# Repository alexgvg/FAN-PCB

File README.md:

# FAN-PCB
Leiterkarte für FAN Stromverteilung

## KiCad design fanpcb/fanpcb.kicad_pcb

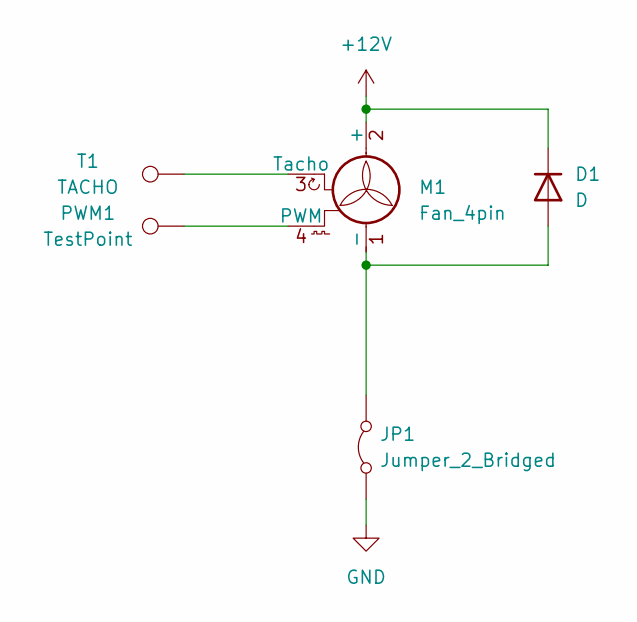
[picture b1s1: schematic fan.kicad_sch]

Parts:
D1: D; D_0603_1608Metric_Pad1.05x0.95mm_HandSolder
JP1: Jumper_2_Bridged; PinHeader_1x02_P2.54mm_Vertical
M1: Fan_4pin; FanPinHeader_1x04_P2.54mm_Vertical
PWM1: TestPoint; TestPoint_Pad_D2.5mm
T1: TACHO; TestPoint_Pad_D2.5mm

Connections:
+12V: D1.1 (K), M1.2 (+); also elsewhere on the board
GND: JP1.1 (A); also elsewhere on the board
unnamed: D1.2 (A), JP1.2 (B), M1.1 (-)
unnamed: M1.4 (PWM), PWM1.1 (1_1)
unnamed: M1.3 (Tacho), T1.1 (1_1)

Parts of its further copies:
D2, D3: D; D_0603_1608Metric_Pad1.05x0.95mm_HandSolder
JP2, JP3: Jumper_2_Bridged; PinHeader_1x02_P2.54mm_Vertical
M2, M3: Fan_4pin; FanPinHeader_1x04_P2.54mm_Vertical
PWM2, PWM3: TestPoint; TestPoint_Pad_D2.5mm
T2, T3: TACHO; TestPoint_Pad_D2.5mm

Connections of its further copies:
+12V: D2.1 (K), D3.1 (K), M2.2 (+), M3.2 (+); also elsewhere on the board
GND: JP2.1 (A), JP3.1 (A); also elsewhere on the board
unnamed: D2.2 (A), JP2.2 (B), M2.1 (-)
unnamed: D3.2 (A), JP3.2 (B), M3.1 (-)
unnamed: M2.4 (PWM), PWM2.1 (1_1)
unnamed: M2.3 (Tacho), T2.1 (1_1)
unnamed: M3.4 (PWM), PWM3.1 (1_1)
unnamed: M3.3 (Tacho), T3.1 (1_1)

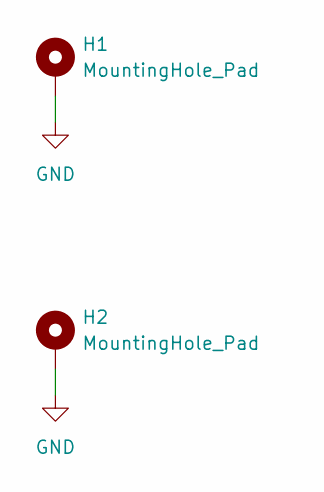
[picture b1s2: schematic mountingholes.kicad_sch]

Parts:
H1, H2: MountingHole_Pad; MountingHole_3.2mm_M3_DIN965_Pad_TopBottom

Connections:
GND: H1.1 (1_1), H2.1 (1_1); also elsewhere on the board

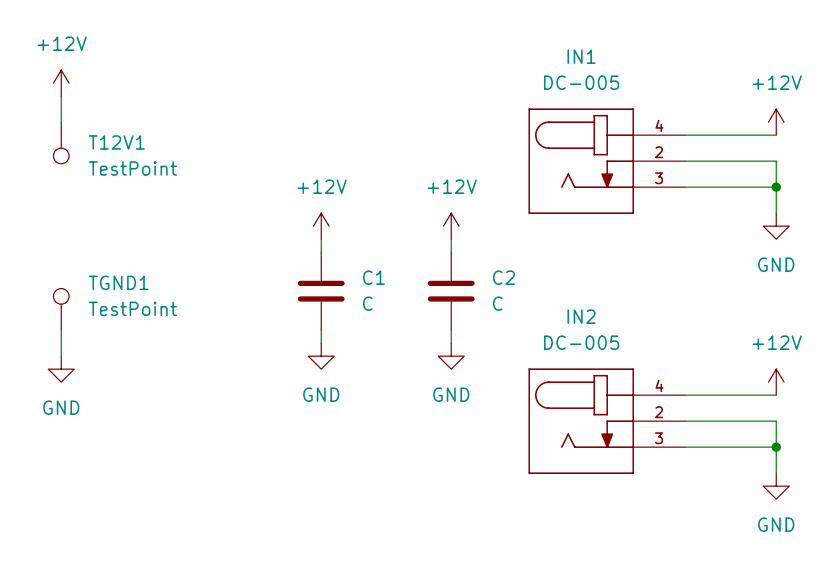
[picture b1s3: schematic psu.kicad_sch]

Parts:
C1: C; C_1206_3216Metric_Pad1.33x1.80mm_HandSolder
C2: C; C_0603_1608Metric_Pad1.08x0.95mm_HandSolder
IN1, IN2: DC-005; NINIGI_DC-005
T12V1: TestPoint; TestPoint_Pad_D2.5mm
TGND1: TestPoint; TestPoint_Pad_D2.5mm

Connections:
+12V: C1.1, C2.1, IN1.4, IN2.4, T12V1.1 (1_1); also elsewhere on the board
GND: C1.2, C2.2, IN1.2, IN1.3, IN2.2, IN2.3, TGND1.1 (1_1); also elsewhere on the board

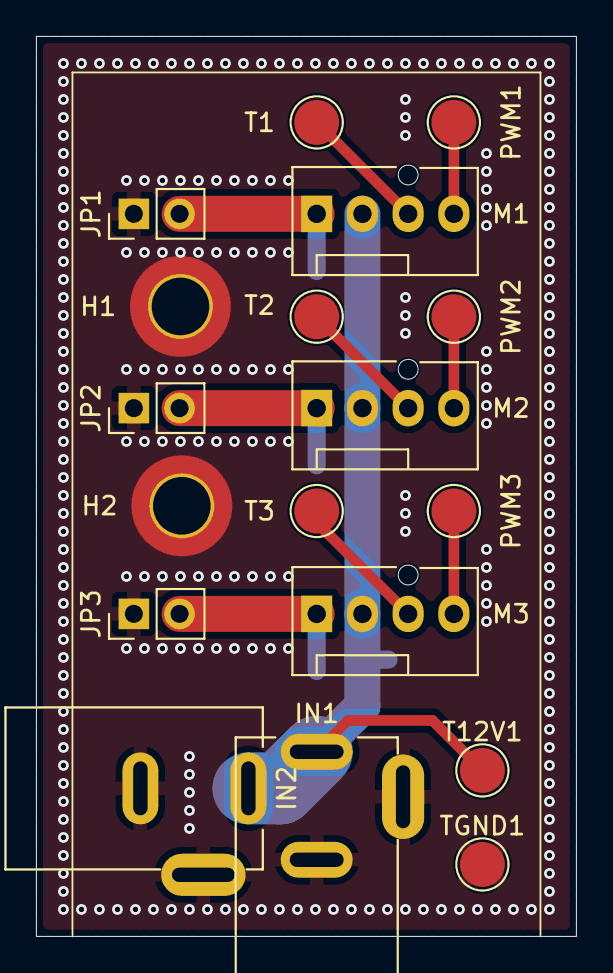
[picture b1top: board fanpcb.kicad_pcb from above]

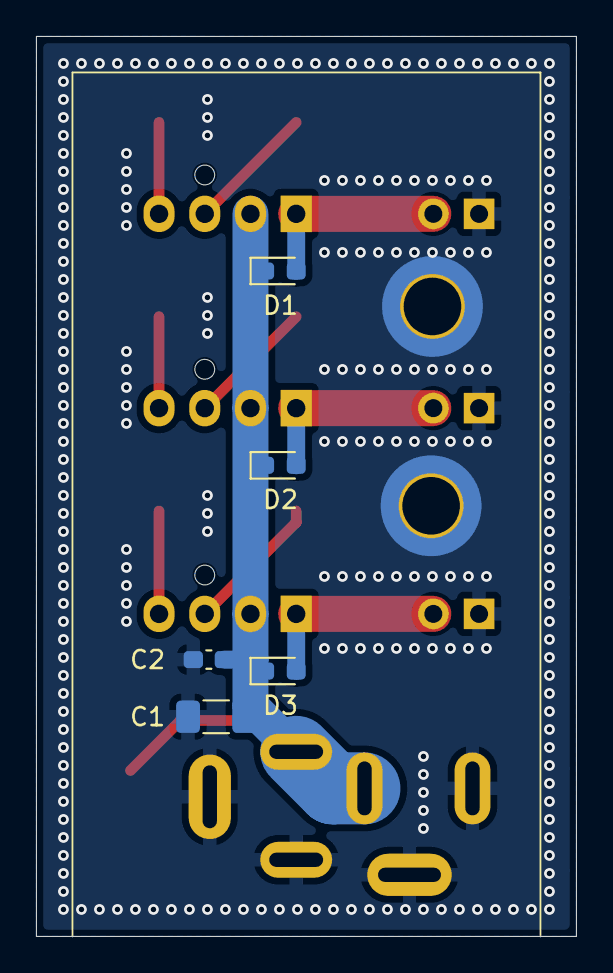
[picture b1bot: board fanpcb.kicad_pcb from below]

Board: 2 copper layers, 30.0 x 50.0 mm, 23 parts (5 on the bottom side), 11 nets.
